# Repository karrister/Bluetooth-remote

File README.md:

Bluetooth-remote
=============

A project to make a simple multi-purpose Bluetooth remote controller device.

Currently there are two purposes for this project - one is to serve as a Bluetooth shutter for my Nikon SLR, and the second is to integrate the Bluetooth remote to work with my other project, the StigaGoalSong, to be able to control with over the Bluetooth, when a team scores in the game of table hockey (please take a look at my other project in github, StigaGoalSong).

This repository will have one common PCB design for both purposes, and it will also end up including the PIC FW for both cases (unless I will be able to pack both features in one FW).

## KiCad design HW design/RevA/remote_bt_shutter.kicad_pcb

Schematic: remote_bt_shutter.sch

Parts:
C1: TBD
C2, C3: 15pF
C4, C5: 0.1uF
C6: 100pF
C7: 33nF
C8, C9: CP1
D1, D2: TBD
D3, D4: LED
D5: DIODESCH
D6: 0
K1: NIKON_CONN
L1: INDUCTOR
P1: ICSP
P3: MODE_SW
P4: SW1
P5: TP_BT_RX
P6: TP_BT_TX
P7: SW2
P8: SW3
P9: BATT_CONN
P10: PWR_SW
R1: TBD
R2: 0
R3, R4, R6, R7, R8, R11, R13: 10k
R5: 4k6
R9, R10: 200
R12, R15, R16, R17: R
R14: 1K8
T1, T2: BSV52
U1: PIC18F14K50
U2: EGBT-046S
U3: TPS61006
X1: CRYSTAL

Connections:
+3.3V: C4.1, C5.2, C8.1, D5.2 (K), D6.1 (A), D6.2 (K), P1.2, R1.1, R6.1, R7.1, R8.1, R11.1, R15.1, U1.1 (Vdd), U2.12 (Vcc), U3.5 (Vout)
/LOW_BATT_IND: D1.1 (A), R15.2, U3.10 (LBO)
GND: C1.2, C2.2, C3.2, C4.2, C5.1, C6.2, C7.2, C8.2, C9.2, D3.2 (K), D4.2 (K), K1.1, P1.3, P3.1, P4.1, P7.1, P8.1, P9.2 (PM), R16.2, T1.2 (E), U1.20 (Vss), U2.13 (GND), U2.22 (GND), U3.4 (GND)
unnamed: D1.2 (K), D2.2 (K), P1.1, U1.4 (RA3/MCLR)
unnamed: C1.1, D2.1 (A), R1.2
unnamed: P9.1, P10.2 (PM)
unnamed: P1.5, U1.18 (RA1/D-)
unnamed: C7.1, R13.2
unnamed: R14.2, U3.1 (EN)
unnamed: P7.2 (PM), R7.2, U1.15 (RC1/AN5/INT1)
unnamed: P4.2 (PM), R6.2, U1.16 (RC0/AN4/INT0)
unnamed: P1.4, U1.19 (RA0/D+)
unnamed: R9.1, U1.13 (RB4/AN10/SDI/SDA)
unnamed: D3.1 (A), R9.2
unnamed: R12.2, U1.9 (RC7/AN9/SDO)
unnamed: R12.1, U2.24 (LED1)
unnamed: C9.1, L1.1, P10.1, R14.1, R17.1, U3.6 (Vbat)
unnamed: R16.1, R17.2, U3.9 (LBI)
unnamed: R10.1, U1.7 (RC3/AN7)
unnamed: K1.3, T2.3 (C)
unnamed: C6.1, R13.1, U3.2 (COMP)
unnamed: D4.1 (A), R10.2
unnamed: P8.2 (PM), R11.2, U1.11 (RB6/SCK)
unnamed: P3.2 (PM), R8.2, U1.14 (RC2/AN6/INT2)
unnamed: R4.2, T2.1 (B)
unnamed: R3.1, U1.5 (RC5/CCP1)
unnamed: C3.1, R2.1, R2.2, U1.3 (RA4/OSC2), X1.2
unnamed: C2.1, U1.2 (RA5/OSC1), X1.1
unnamed: K1.2 (PM), T1.3 (C), T2.2 (E)
unnamed: R3.2, T1.1 (B)
unnamed: P6.1, U1.12 (RB5/AN11/RX), U2.1 (TXD)
unnamed: P5.1, U1.10 (RB7/TX), U2.2 (RXD)
unnamed: R5.1, U1.8 (RC6/AN8/SS)
unnamed: R4.1, U1.6 (RC4/P1B)
unnamed: R5.2, U2.11 (RESET)
unnamed: D5.1 (A), L1.2, U3.7 (SW)

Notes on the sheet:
POWER INPUT CIRCUIT 1.5V TO 3.3V BOOST

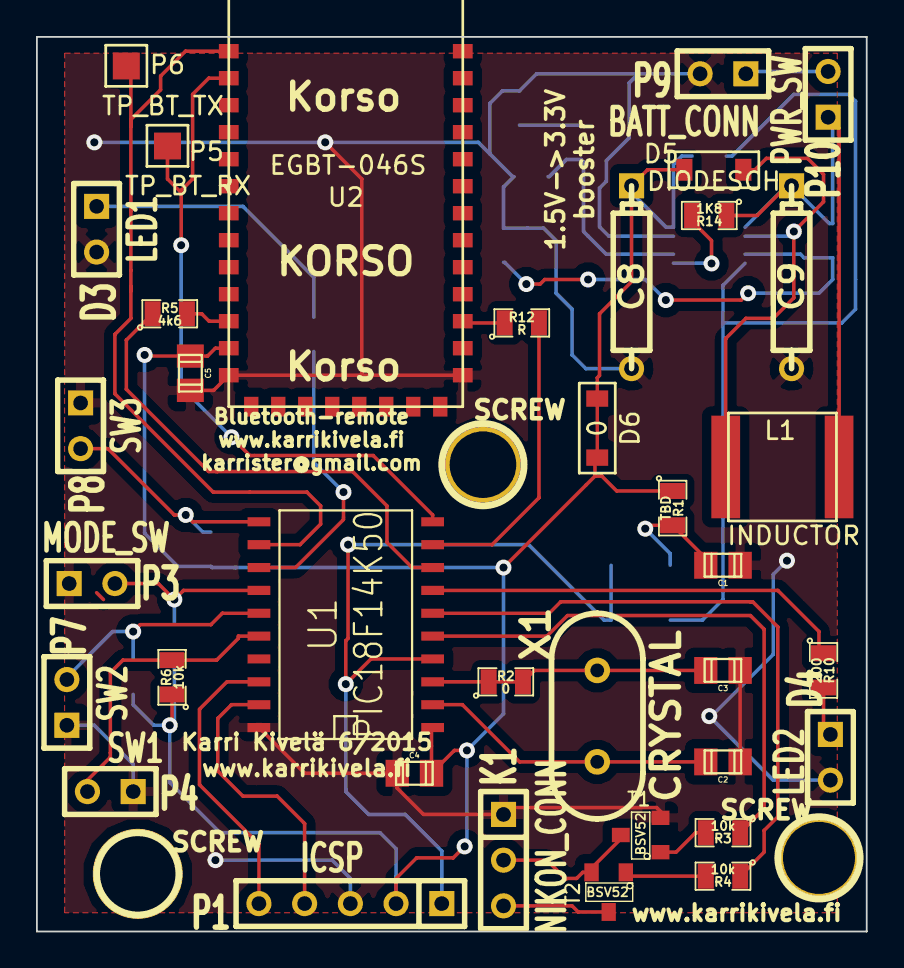
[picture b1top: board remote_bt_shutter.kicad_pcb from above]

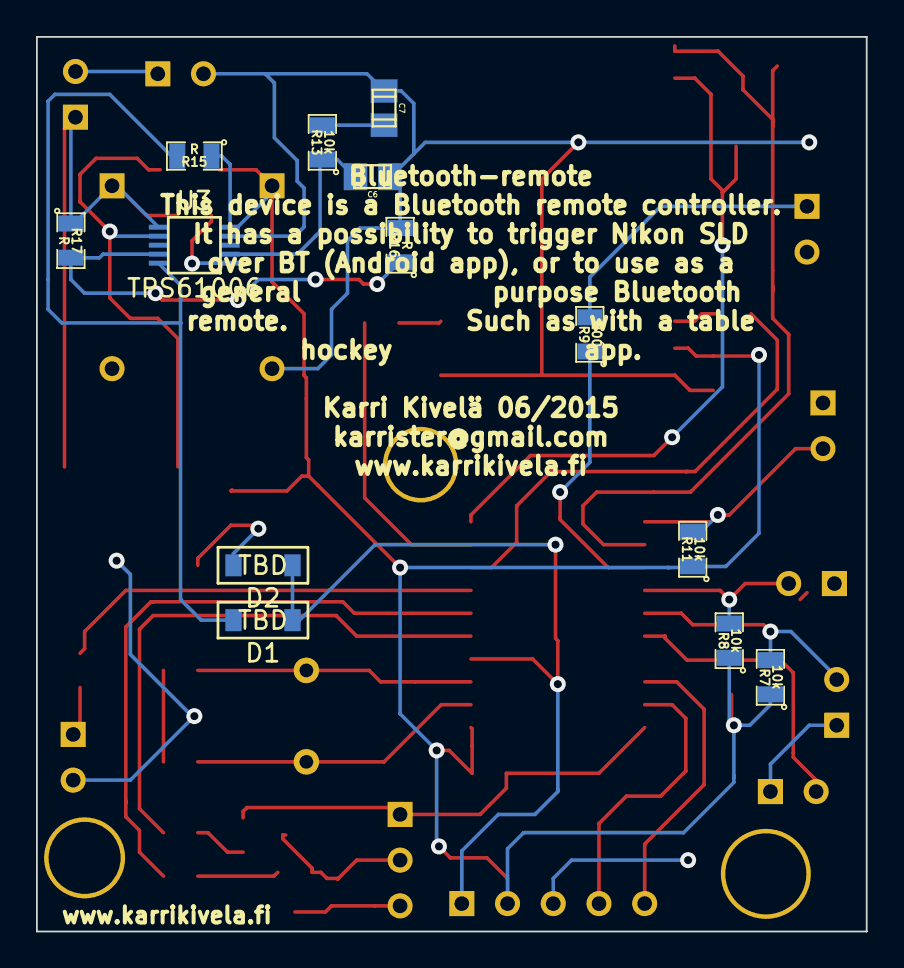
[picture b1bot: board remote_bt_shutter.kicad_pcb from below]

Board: 2 copper layers, 46.1 x 49.7 mm, 52 parts (13 on the bottom side), 36 nets.

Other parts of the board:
SCREW: P***; 1pin
SCREW#2, SCREW#3: P***; 1pin

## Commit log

2015-06-13 :confetti_ball: Added .gitattributes
2015-06-13 The initial commit with some PCB logic
    Some previously done work on the PCB logic of a remote Bluetooth shutter
    design. Will base the project on top of this HW design.
2015-06-13 Readme
    Writing a readme cover for the project.
2015-06-14 More work on the PCB logic
    More work, added two switches switch and a LED.
2015-06-20 Finished PCB logic design
    PCB logic design finished.
2015-06-20 Netlist before the new footprints
    Parts netlist done, other than for the parts that need footprints
    created.
2015-06-20 Adding kicad_parts as a subproject
2015-06-20 More netlist done
    More netlist and footprints done, only BT module and coil lacking.
2015-06-21 Misc changes
2015-06-21 squash
2015-06-22 Some work on PCB layout
    Started to work on PCB layout. Layout almost finished.
2015-06-22 Added a diode from power circuit
    To be on the safe side, added a diode to protect the power circuit from any current from the ICSP prommer. Is actually a shorted connector which can be in time of catastrophy have the trace cut and d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
2015-06-22 PCB layout almost done
    PCB layout done otherwise except for front ground
2015-06-22 PCB layout finished
    Layout finished, still need to add board edges
2015-06-23 PCB layout final
    PCB layout finished, ready for printing.
2015-06-23 PCB printing
    PCB gerber files, printing ordered.
2015-06-23 FW initial commit
    Initial commit of the FW. Started working on the Firmware for PIC. Only
    project started and some source files created.
2015-06-24 Pinout
    Added pinout comment, init stub
2015-06-27 Work on the init
    Some work on the init code
2015-07-11 Basic main logic
    The basic main logic implemented in the PIC Firmware. Need to add some
    more init of peripherals and read of buttons/gpio state.
